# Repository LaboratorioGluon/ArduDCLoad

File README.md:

# ArduDCLoad	

A configurable multipurpose DC Load board developed directly [on Twitch](https://www.twitch.tv/labgluon)

The values of the resistors can be calculated to adapt the PCB to your needs.

With defaul values máximum values are:
- V_TEST: 15V, 3A
- V_In; 5V

And this is how it looks:

# Design and customization

Here we will see how to customize the circuit for our need. The ADCL (ArduDCLoad) can be configure to mount a beefy TO-247 or small TO-220 MOSFETS. Also, it also contains the footprint for 10 resistors( L: 10mm, D: 3.6mm, P:15mm) or big chunky wirewound resistor (L:50mm, W:14mm).

Lets see how to adapt it to your need (we will calculate the values for the current values in the design)

## Select V_TEST and I_TEST

Set what do you need for V_TEST and I_TEST. The circuit can only support **around 5-6A** máximum.

In our case

> V_TEST = 15V
> I_TEST = 3A

## Select MOSFET measuring resistor

The ideal values would be between 1 to 0.1 Ohms. The lower the current you expect, the bigget the value should be. In our case, for 3A, with 1 Ohm, we have 3V drop, so we can go with 1 Ohm. (We expect to test more than 3V)

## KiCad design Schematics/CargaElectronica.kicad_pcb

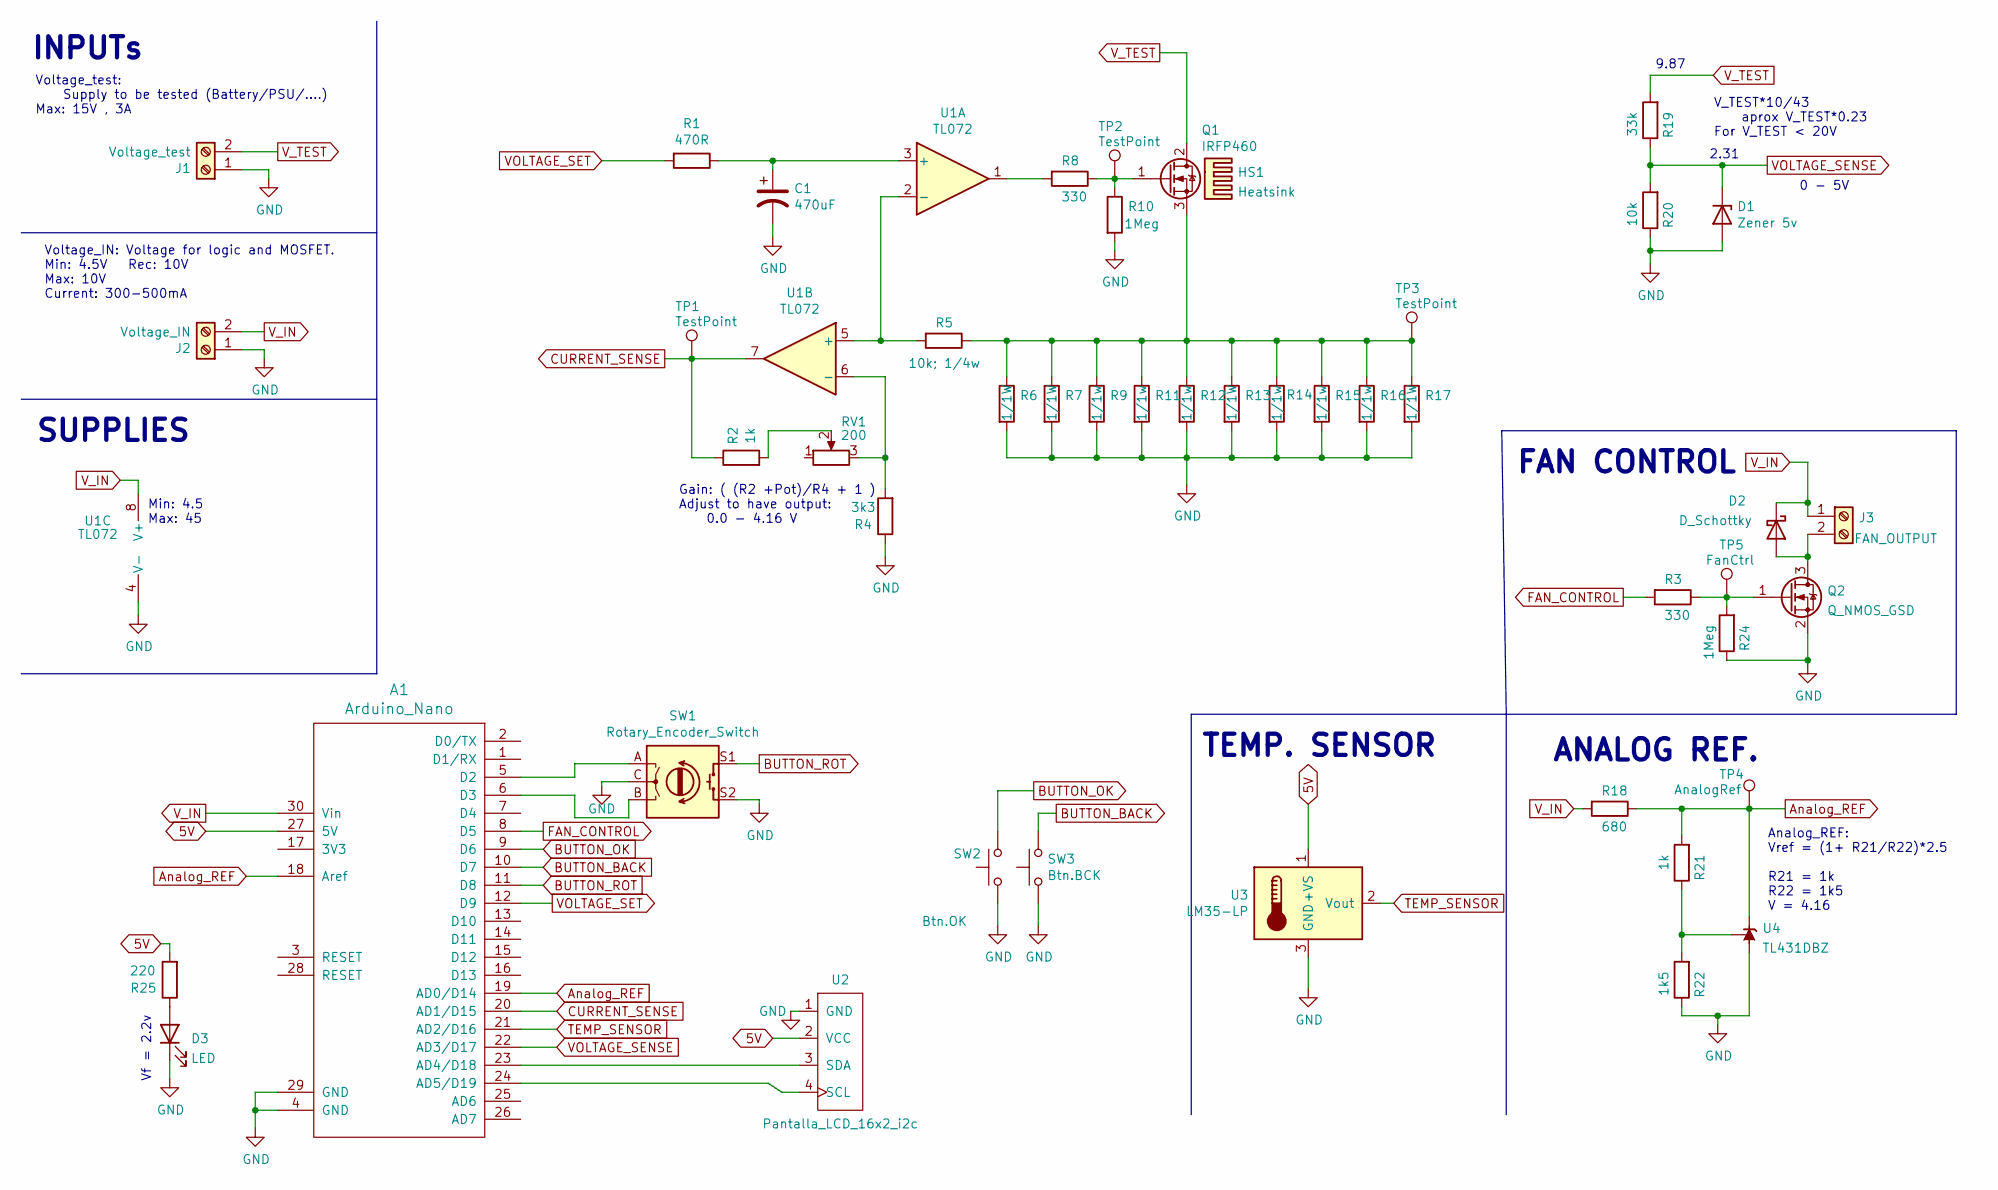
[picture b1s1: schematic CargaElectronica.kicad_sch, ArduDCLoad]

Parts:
A1: Arduino_Nano; arduino_nano
C1: 470uF; CP_Radial_D8.0mm_P3.50mm
D1: Zener 5v; D_A-405_P10.16mm_Horizontal
D2: D_Schottky; D_SOD-323_HandSoldering
D3: LED; LED_D5.0mm_Horizontal_O1.27mm_Z3.0mm
HS1: Heatsink
J1: Voltage_test; TerminalBlock_bornier-2_P5.08mm
J2: Voltage_IN; TerminalBlock_bornier-2_P5.08mm
J3: FAN_OUTPUT; PinHeader_1x02_P2.54mm_Vertical
Q1: IRFP460; TO-247-3_Vertical
Q2: Q_NMOS_GSD; SOT-23
R1: 470R; R_1206_3216Metric_Pad1.30x1.75mm_HandSolder
R2, R21: 1k; R_1206_3216Metric_Pad1.30x1.75mm_HandSolder
R3, R8: 330; R_1206_3216Metric_Pad1.30x1.75mm_HandSolder
R4: 3k3; R_1206_3216Metric_Pad1.30x1.75mm_HandSolder
R5: 10k; 1/4w; R_1206_3216Metric_Pad1.30x1.75mm_HandSolder
R6, R7, R13, R17: 1/1W; R_Axial_DIN0411_L9.9mm_D3.6mm_P15.24mm_Horizontal
R9, R11, R12, R14, R15, R16: 1/1w; R_Axial_DIN0411_L9.9mm_D3.6mm_P15.24mm_Horizontal
R10, R24: 1Meg; R_1206_3216Metric_Pad1.30x1.75mm_HandSolder
R18: 680; R_1206_3216Metric_Pad1.30x1.75mm_HandSolder
R19: 33k; R_1206_3216Metric_Pad1.30x1.75mm_HandSolder
R20: 10k; R_1206_3216Metric_Pad1.30x1.75mm_HandSolder
R22: 1k5; R_1206_3216Metric_Pad1.30x1.75mm_HandSolder
R25: 220; R_1206_3216Metric_Pad1.30x1.75mm_HandSolder
RV1: 200; Potentiometer_Bourns_3296W_Vertical
SW1: Rotary_Encoder_Switch; RotaryEncoder_Alps_EC11E-Switch_Vertical_H20mm
SW2: Btn.OK; SW_PUSH_6mm_H4.3mm
SW3: Btn.BCK; SW_PUSH_6mm_H4.3mm
TP1, TP2, TP3: TestPoint; TestPoint_Pad_D2.0mm
TP4: AnalogRef; TestPoint_Pad_D2.0mm
TP5: FanCtrl; TestPoint_Pad_D2.0mm
U1: TL072; SOIC-8_3.9x4.9mm_P1.27mm
U2: Pantalla_LCD_16x2_i2c; PinHeader_1x04_P2.54mm_Horizontal
U3: LM35-LP; TO-92_Inline_Wide
U4: TL431DBZ; SOT-23

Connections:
5V: A1.27 (5V), R25.2, U2.2 (VCC), U3.1 (+VS)
Analog_REF: A1.18 (Aref), A1.19 (AD0/D14), R18.1, R21.2, TP4.1, U4.1 (K)
BUTTON_BACK: A1.10 (D7), SW3.2
BUTTON_OK: A1.9 (D6), SW2.2
BUTTON_ROT: A1.11 (D8), SW1.S1
CURRENT_SENSE: A1.20 (AD1/D15), R2.1, TP1.1, U1.7
FAN_CONTROL: A1.8 (D5), R3.2
GND: A1.4 (GND), A1.29 (GND), C1.2, D1.2 (A), D3.1 (K), J1.1, J2.1, Q2.2 (S), R4.1, R6.2, R7.2, R9.2, R10.2, R11.2, R12.2, R13.2, R14.2, R15.2, R16.2, R17.2, R20.1, R22.1, R24.1, SW1.C, SW1.S2, SW2.1, SW3.1, U1.4 (V-), U2.1 (GND), U3.3 (GND), U4.3 (A)
unnamed: A1.5 (D2), SW1.A
unnamed: A1.6 (D3), SW1.B
unnamed: A1.23 (AD4/D18), U2.3 (SDA)
unnamed: A1.24 (AD5/D19), U2.4 (SCL)
unnamed: C1.1, R1.1, U1.3 (+)
unnamed: D2.2 (A), J3.2, Q2.3 (D)
unnamed: D3.2 (A), R25.1
unnamed: Q1.1 (G), R8.1, R10.1, TP2.1
unnamed: Q1.3 (S), R5.1, R6.1, R7.1, R9.1, R11.1, R12.1, R13.1, R14.1, R15.1, R16.1, R17.1, TP3.1
unnamed: Q2.1 (G), R3.1, R24.2, TP5.1
unnamed: R2.2, RV1.2
unnamed: R4.2, RV1.3, U1.6 (-)
unnamed: R5.2, U1.2 (-), U1.5 (+)
unnamed: R8.2, U1.1
unnamed: R21.1, R22.2, U4.2 (REF)
TEMP_SENSOR: A1.21 (AD2/D16), U3.2 (Vout)
VOLTAGE_SENSE: A1.22 (AD3/D17), D1.1 (K), R19.1, R20.2
VOLTAGE_SET: A1.12 (D9), R1.2
V_IN: A1.30 (Vin), D2.1 (K), J2.2, J3.1, R18.2, U1.8 (V+)
V_TEST: J1.2, Q1.2 (D), R19.2

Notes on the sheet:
Min: 4.5 Max: 45
Vf = 2.2v
ANALOG REF.
INPUTs
9.87
V_TEST*10/43 aprox V_TEST*0.23 For V_TEST < 20V
2.31
TEMP. SENSOR
Voltage_test: Supply to be tested (Battery/PSU/....) Max: 15V , 3A
FAN CONTROL
SUPPLIES
Voltage_IN: Voltage for logic and MOSFET. Min: 4.5V Rec: 10V Max: 10V Current: 300-500mA
Analog_REF: Vref = (1+ R21/R22)*2.5 R21 = 1k R22 = 1k5 V = 4.16
Gain: ( (R2 +Pot)/R4 + 1 ) Adjust to have output: 0.0 - 4.16 V
0 - 5V

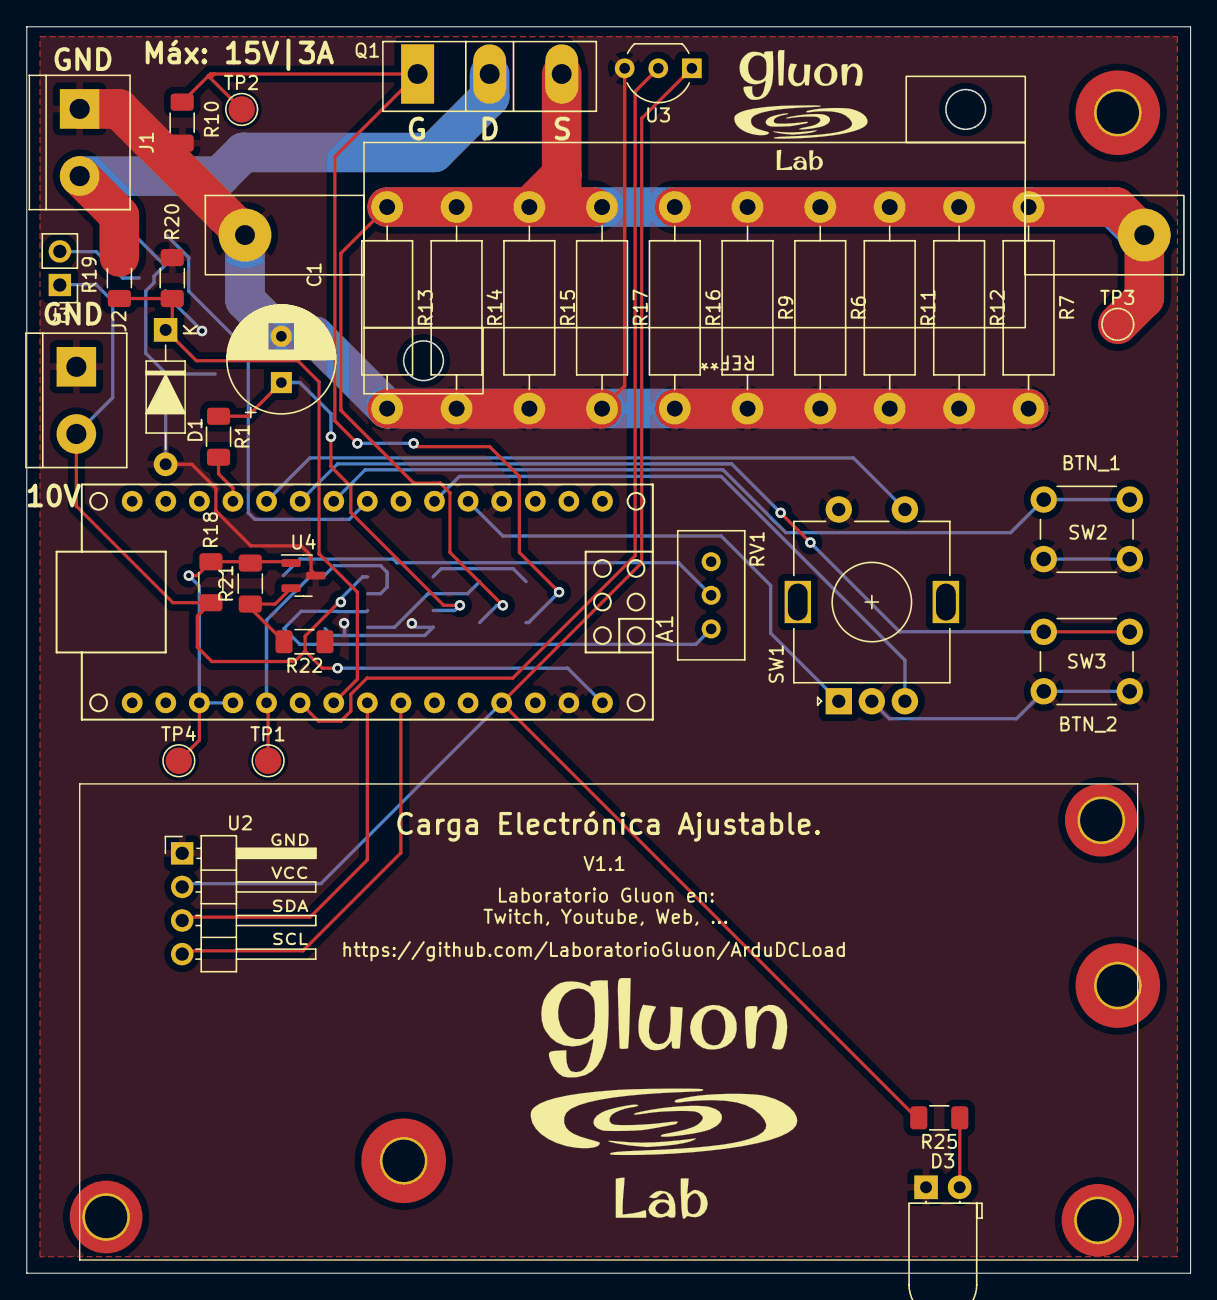
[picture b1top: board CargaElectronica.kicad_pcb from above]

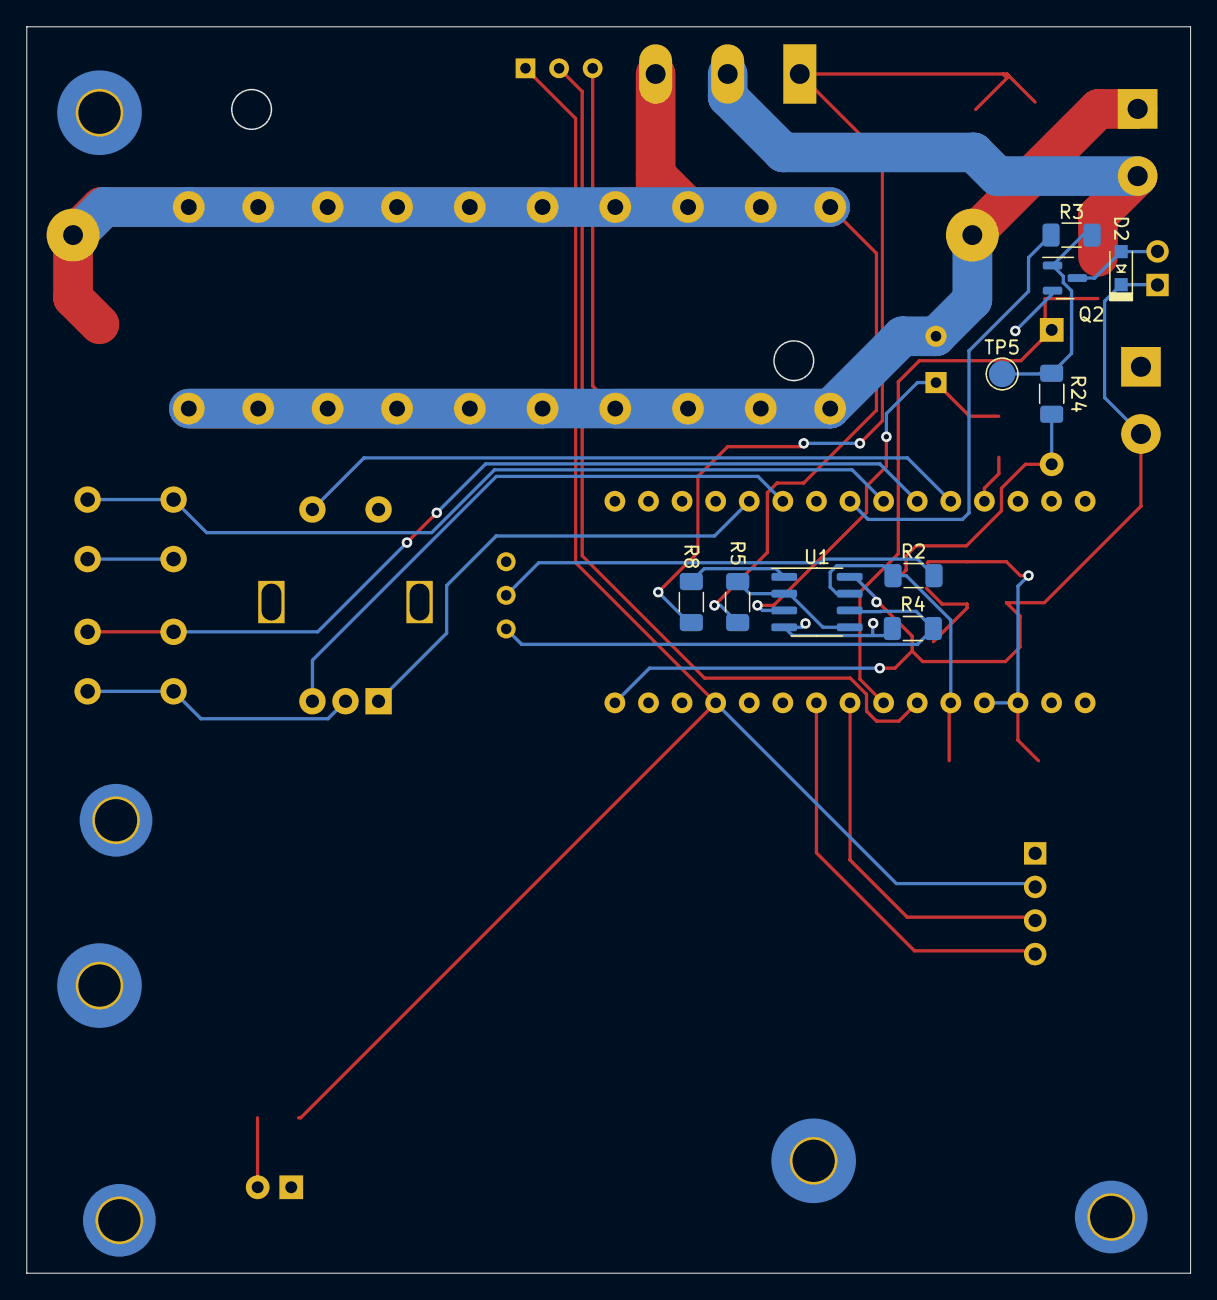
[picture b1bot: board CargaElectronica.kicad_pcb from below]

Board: 2 copper layers, 87.9 x 94.2 mm, 47 parts (10 on the bottom side), 28 nets.

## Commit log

2021-11-13 PCB, Schematic, code not valid
2021-11-13 Deleted backup files from git
2021-11-13 Added README
2021-11-13 Imagen y documentos de la PCB
2021-11-13 Added image to README
2021-11-13 Updated REadme, again
2021-11-13 Modified PCB
2021-11-13 Changed the PCB image
2021-11-14 Added Fan interface
2021-11-14 Updated schematic, did not update with last commit
2021-12-09 Intermediate commit, pre-update to new kicad
2021-12-09 Fixed errors in PCB routing
2021-12-12 Intermediate commit
2021-12-12 Version 1.1, fixes de la PCB
2021-12-21 Fix for PCB v1 and more sourcecode
2022-03-09 Version stable
2024-01-01 added missing FSM
2026-01-02 Minor fix
